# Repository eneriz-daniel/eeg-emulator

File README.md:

# EEG Emulation and Acquisition

> Documentation is available at: [https://eneriz-daniel.com/eeg-emulator/](https://eneriz-daniel.com/eeg-emulator/)

This repository contains the design files, code, and documentation for an EEG
emulation and acquisition system. The system is designed to emulate an EEG headset
using a custom PCB that demultiplexes signals from a National Instruments
USB-6212 Data Acquisition (DAQ) device, and to acquire EEG signals using an ADS1299
Analog-to-Digital Converter (ADC) connected to an Arduino Nano 33 BLE Sense.

## Repository Structure

The repository is organized into the following main directories and files:

- `docs/`: Documentation files for the project
    - `ads1299_driver/`: Python API reference for the ADS1299 driver
    - `assets/`: Images and diagrams used in documentation
    - `datasheets/`: Component datasheets and manuals
  
- `eeg_acquisition/`: EEG signal acquisition system components
    - `ADS1299driver.py`: Python wrapper for the ADS1299 driver
    - `design_files/`: KiCAD PCB and schematic files for the acquisition board
    - `micro/`: Arduino firmware for the ADS1299 driver
        - `src/`: C++ source code for the driver implementation

- `eeg_emulation/`: EEG signal emulation system components
    - `daq.py`: Python script for controlling the NI USB-6212 DAQ
    - `design_files/`: KiCAD PCB and schematic files for the demultiplexer board

- `test.py`: Example script demonstrating the integration between the EEG emulation and acquisition systems, including configuration of the ADS1299, signal generation, data acquisition, and visualization

## Requirements

### Software

- [Python](https://www.python.org/) 3.13 or later (for running the code and documentation)
    - Package manager, [`uv`](https://docs.astral.sh/uv/)
- [KiCAD](https://www.kicad.org/) 9 or later (for PCB design files)
- [PlatformIO](https://platformio.org/) (for Arduino development)

### Commercial hardware

- National Instruments NI USB-6212 Data Acquisition device

## Installation

- Clone the repository:

    ```bash
    git clone https://github.com/eneriz-daniel/eeg-emulator.git
    ```

- Install the required packages:

    ```bash
    uv sync --all-groups
    ```

## Software commands

- To serve the documentation locally:

    ```bash
    uv run mkdocs serve
    ```

- To check linting and formatting:

    ```bash
    uv run ruff check
    ```

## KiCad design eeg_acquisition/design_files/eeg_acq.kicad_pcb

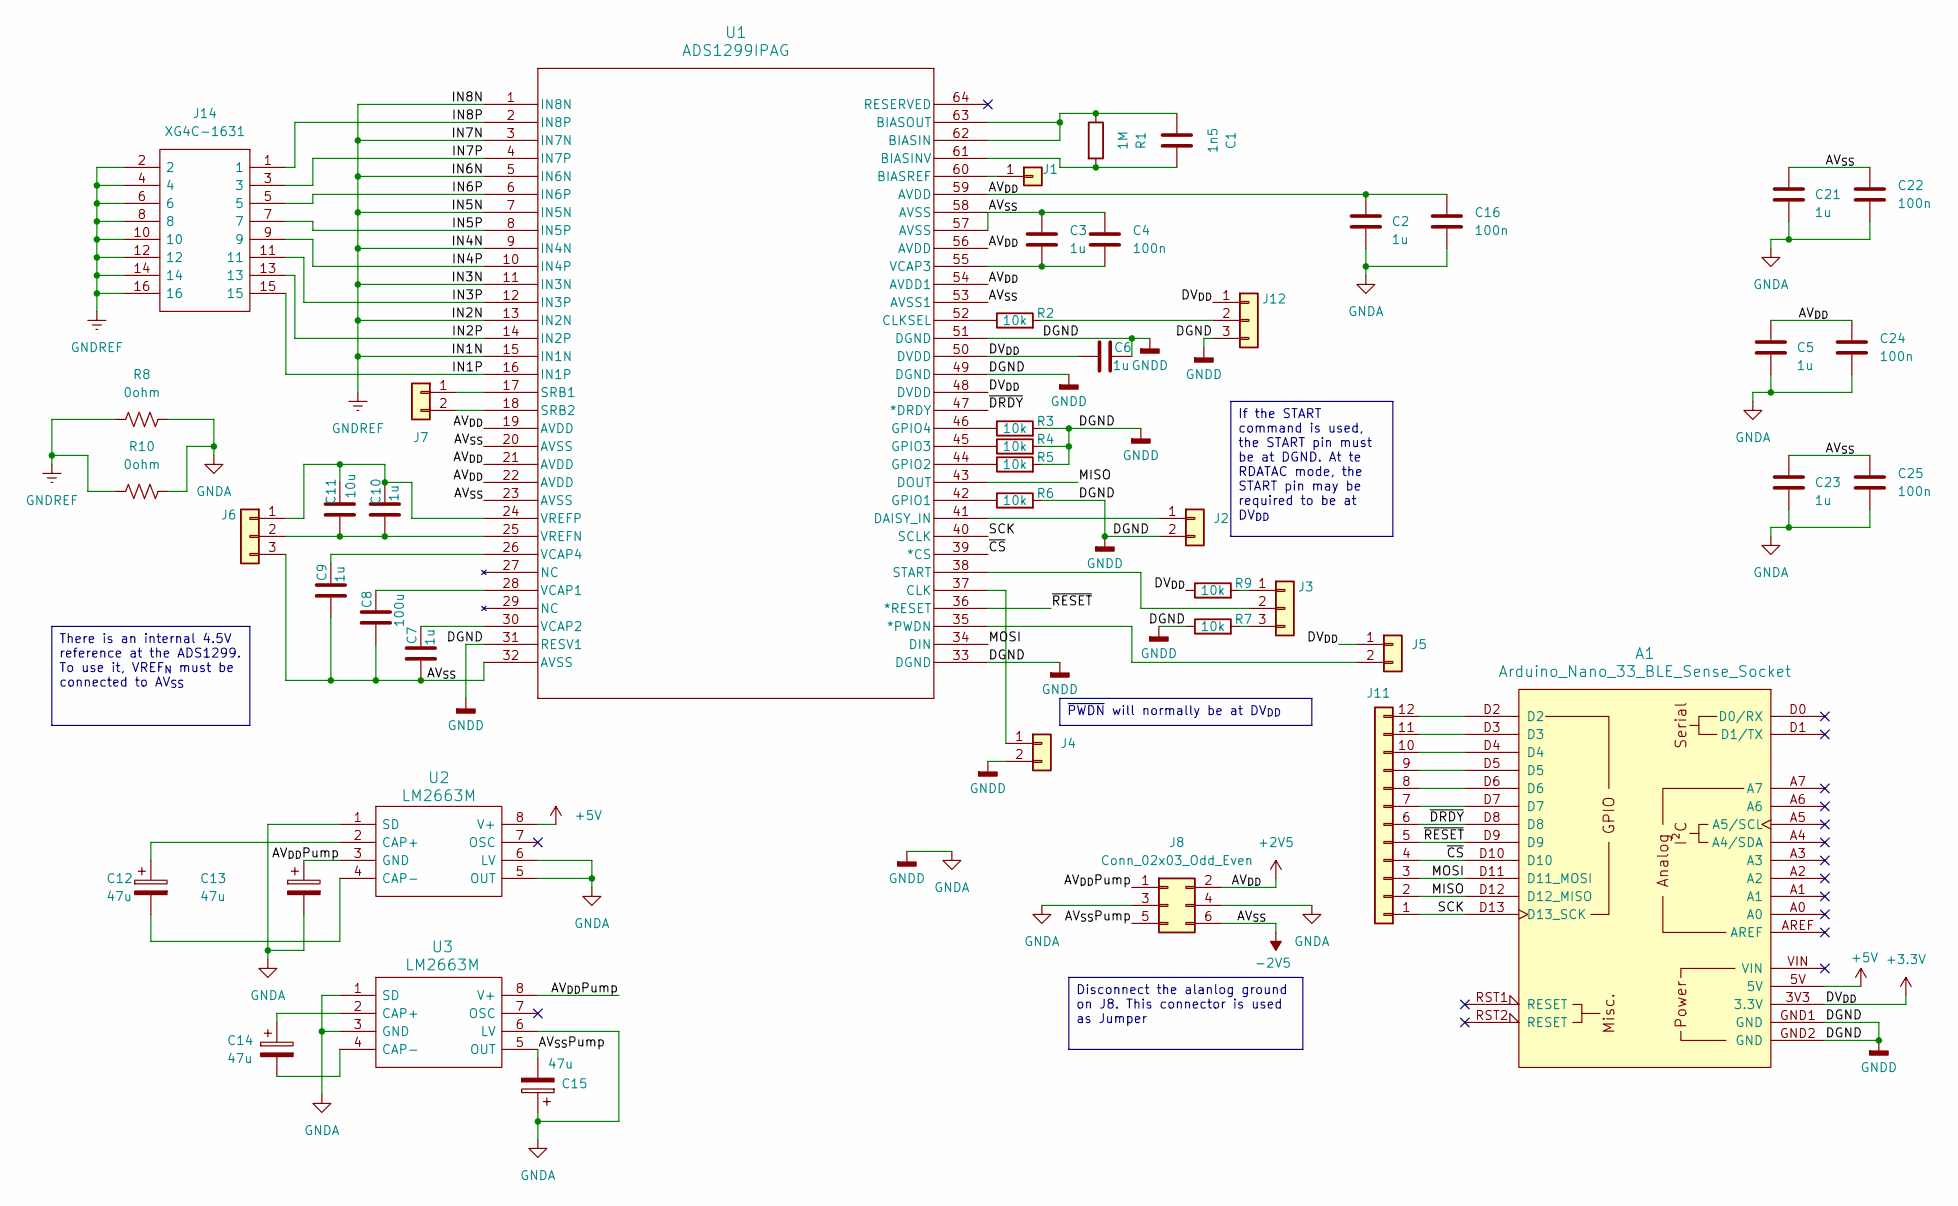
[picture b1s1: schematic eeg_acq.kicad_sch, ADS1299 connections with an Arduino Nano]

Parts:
A1: Arduino_Nano_33_BLE_Sense_Socket; Arduino_Nano_Every_Socket
C1: 1n5; C_0603_1608Metric_Pad1.08x0.95mm_HandSolder
C2, C3, C5, C6, C7, C9, C10, C21, C23: 1u; C_0603_1608Metric_Pad1.08x0.95mm_HandSolder
C4, C16, C22, C24, C25: 100n; C_0603_1608Metric_Pad1.08x0.95mm_HandSolder
C8: 100u; C_1206_3216Metric_Pad1.33x1.80mm_HandSolder
C11: 10u; C_0603_1608Metric_Pad1.08x0.95mm_HandSolder
C12, C13, C14, C15: 47u; CP_Radial_D10.0mm_P5.00mm
J1: BIASREF; PinSocket_1x01_P2.54mm_Vertical
J2, J4: DAISY_IN; PinSocket_1x02_P2.54mm_Vertical
J3: START; PinSocket_1x03_P2.54mm_Vertical
J5: ~PWDN; PinSocket_1x02_P2.54mm_Vertical
J6: VREF; PinSocket_1x03_P2.54mm_Vertical
J7: SRB; PinSocket_1x02_P2.54mm_Vertical
J8: Conn_02x03_Odd_Even; PinHeader_2x03_P2.54mm_Vertical
J11: PinHeader_1x12_P2.54mm_Vertical
J12: CLKSEL; PinSocket_1x03_P2.54mm_Vertical
J14: XG4C-1631; SHDR16W70P254_2X8_2760X850X900P; Manufacturer_Part_Number XG4C-1631; Mouser Part Number 653-XG4C-1631
R1: 1M; R_0603_1608Metric_Pad0.98x0.95mm_HandSolder
R2, R3, R4, R5, R6, R7, R9: 10k; R_0603_1608Metric_Pad0.98x0.95mm_HandSolder
R8, R10: 0ohm; R_0603_1608Metric
U1: ADS1299IPAG; PAG64_TEX
U2, U3: LM2663M; SOIC127P600X175-8N; Manufacturer_Part_Number LM2663M; Mouser Part Number 926-LM2663M

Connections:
+2V5: C2.1, C5.1, C16.1, C24.1, J8.2, U1.19 (AVDD), U1.21 (AVDD), U1.22 (AVDD), U1.54 (AVDD1), U1.56 (AVDD), U1.59 (AVDD)
+3.3V: A1.3V3 (3.3V), C6.2, J5.1, J12.1, R9.1, U1.48 (DVDD), U1.50 (DVDD)
+5V: A1.5V, U2.8 (V+)
-2V5: C3.1, C4.1, C7.2, C8.2, C9.2, C21.1, C22.1, C23.1, C25.1, J6.3, J8.6, U1.20 (AVSS), U1.23 (AVSS), U1.32 (AVSS), U1.53 (AVSS1), U1.57 (AVSS), U1.58 (AVSS)
/AV_{DD}Pump: C13.1, J8.1, U2.3 (GND), U3.8 (V+)
/AV_{SS}Pump: C15.2, J8.5, U3.5 (OUT)
/IN1P: J14.15, U1.16 (IN1P)
/IN2P: J14.13, U1.14 (IN2P)
/IN3P: J14.11, U1.12 (IN3P)
/IN4P: J14.9, U1.10 (IN4P)
/IN5P: J14.7, U1.8 (IN5P)
/IN6P: J14.5, U1.6 (IN6P)
/IN7P: J14.3, U1.4 (IN7P)
/IN8P: J14.1, U1.2 (IN8P)
/MISO: A1.D12 (D12_MISO), J11.2, U1.43 (DOUT)
/MOSI: A1.D11 (D11_MOSI), J11.3, U1.34 (DIN)
/SCK: A1.D13 (D13_SCK), J11.1, U1.40 (SCLK)
/~CS: A1.D10, J11.4, U1.39 (*CS)
/~DRDY: A1.D8, J11.6, U1.47 (*DRDY)
/~RESET: A1.D9, J11.5, U1.36 (*RESET)
GNDA: A1.GND1 (GND), A1.GND2 (GND), C2.2, C5.2, C6.1, C13.2, C15.1, C16.2, C21.2, C22.2, C23.2, C24.2, C25.2, J2.2, J4.2, J8.3, J8.4, J12.3, R3.2, R4.2, R5.2, R6.2, R7.1, R8.2, R10.2, U1.31 (RESV1), U1.33 (DGND), U1.49 (DGND), U1.51 (DGND), U2.1 (SD), U2.5 (OUT), U2.6 (LV), U3.1 (SD), U3.3 (GND), U3.6 (LV)
GNDREF: J14.2, J14.4, J14.6, J14.8, J14.10, J14.12, J14.14, J14.16, R8.1, R10.1, U1.1 (IN8N), U1.3 (IN7N), U1.5 (IN6N), U1.7 (IN5N), U1.9 (IN4N), U1.11 (IN3N), U1.13 (IN2N), U1.15 (IN1N)
unnamed: J1.1, U1.60 (BIASREF)
unnamed: J2.1, U1.41 (DAISY_IN)
unnamed: J3.1, R9.2
unnamed: J3.2, U1.38 (START)
unnamed: J3.3, R7.2
unnamed: J4.1, U1.37 (CLK)
unnamed: J5.2, U1.35 (*PWDN)
unnamed: C10.1, C11.1, J6.1, U1.24 (VREFP)
unnamed: C10.2, C11.2, J6.2, U1.25 (VREFN)
unnamed: J7.1, U1.17 (SRB1)
unnamed: J7.2, U1.18 (SRB2)
unnamed: A1.D7, J11.7
unnamed: A1.D6, J11.8
unnamed: A1.D5, J11.9
unnamed: A1.D4, J11.10
unnamed: A1.D3, J11.11
unnamed: A1.D2, J11.12
unnamed: J12.2, R2.2
unnamed: C1.1, R1.1, U1.62 (BIASIN), U1.63 (BIASOUT)
unnamed: C1.2, R1.2, U1.61 (BIASINV)
unnamed: R2.1, U1.52 (CLKSEL)
unnamed: R6.1, U1.42 (GPIO1)
unnamed: R5.1, U1.44 (GPIO2)
unnamed: R4.1, U1.45 (GPIO3)
unnamed: R3.1, U1.46 (GPIO4)
unnamed: C8.1, U1.28 (VCAP1)
unnamed: C7.1, U1.30 (VCAP2)
unnamed: C3.2, C4.2, U1.55 (VCAP3)
unnamed: C9.1, U1.26 (VCAP4)
unnamed: C12.1, U2.2 (CAP+)
unnamed: C12.2, U2.4 (CAP-)
unnamed: C14.1, U3.2 (CAP+)
unnamed: C14.2, U3.4 (CAP-)

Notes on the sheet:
~{PWDN} will normally be at DV_{DD}
Disconnect the alanlog ground on J8. This connector is used as Jumper
If the START command is used, the START pin must be at DGND. At te RDATAC mode, the START pin may be required to be at DV_{DD}
There is an internal 4.5V reference at the ADS1299. To use it, VREF_{N} must be connected to AV_{SS}

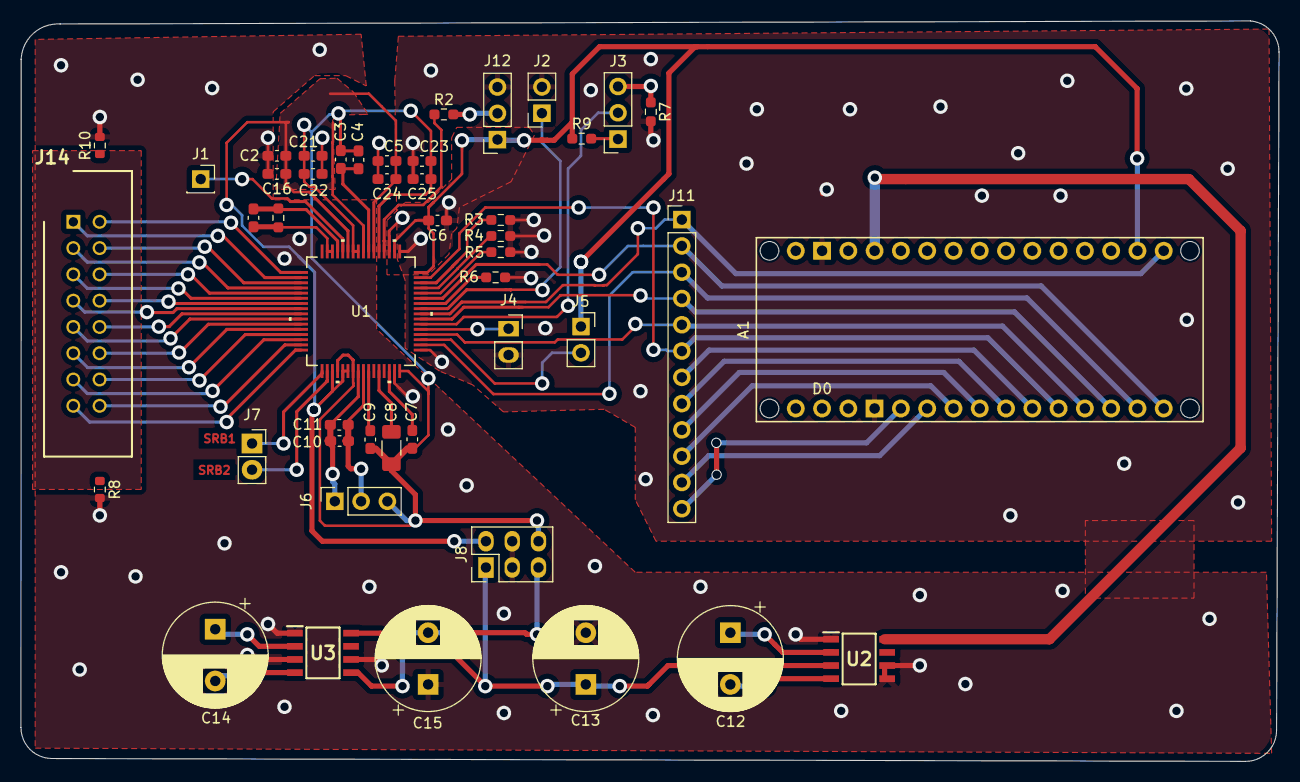
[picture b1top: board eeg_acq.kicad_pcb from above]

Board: 2 copper layers, 121.6 x 71.6 mm, 46 parts (0 on the bottom side), 55 nets.

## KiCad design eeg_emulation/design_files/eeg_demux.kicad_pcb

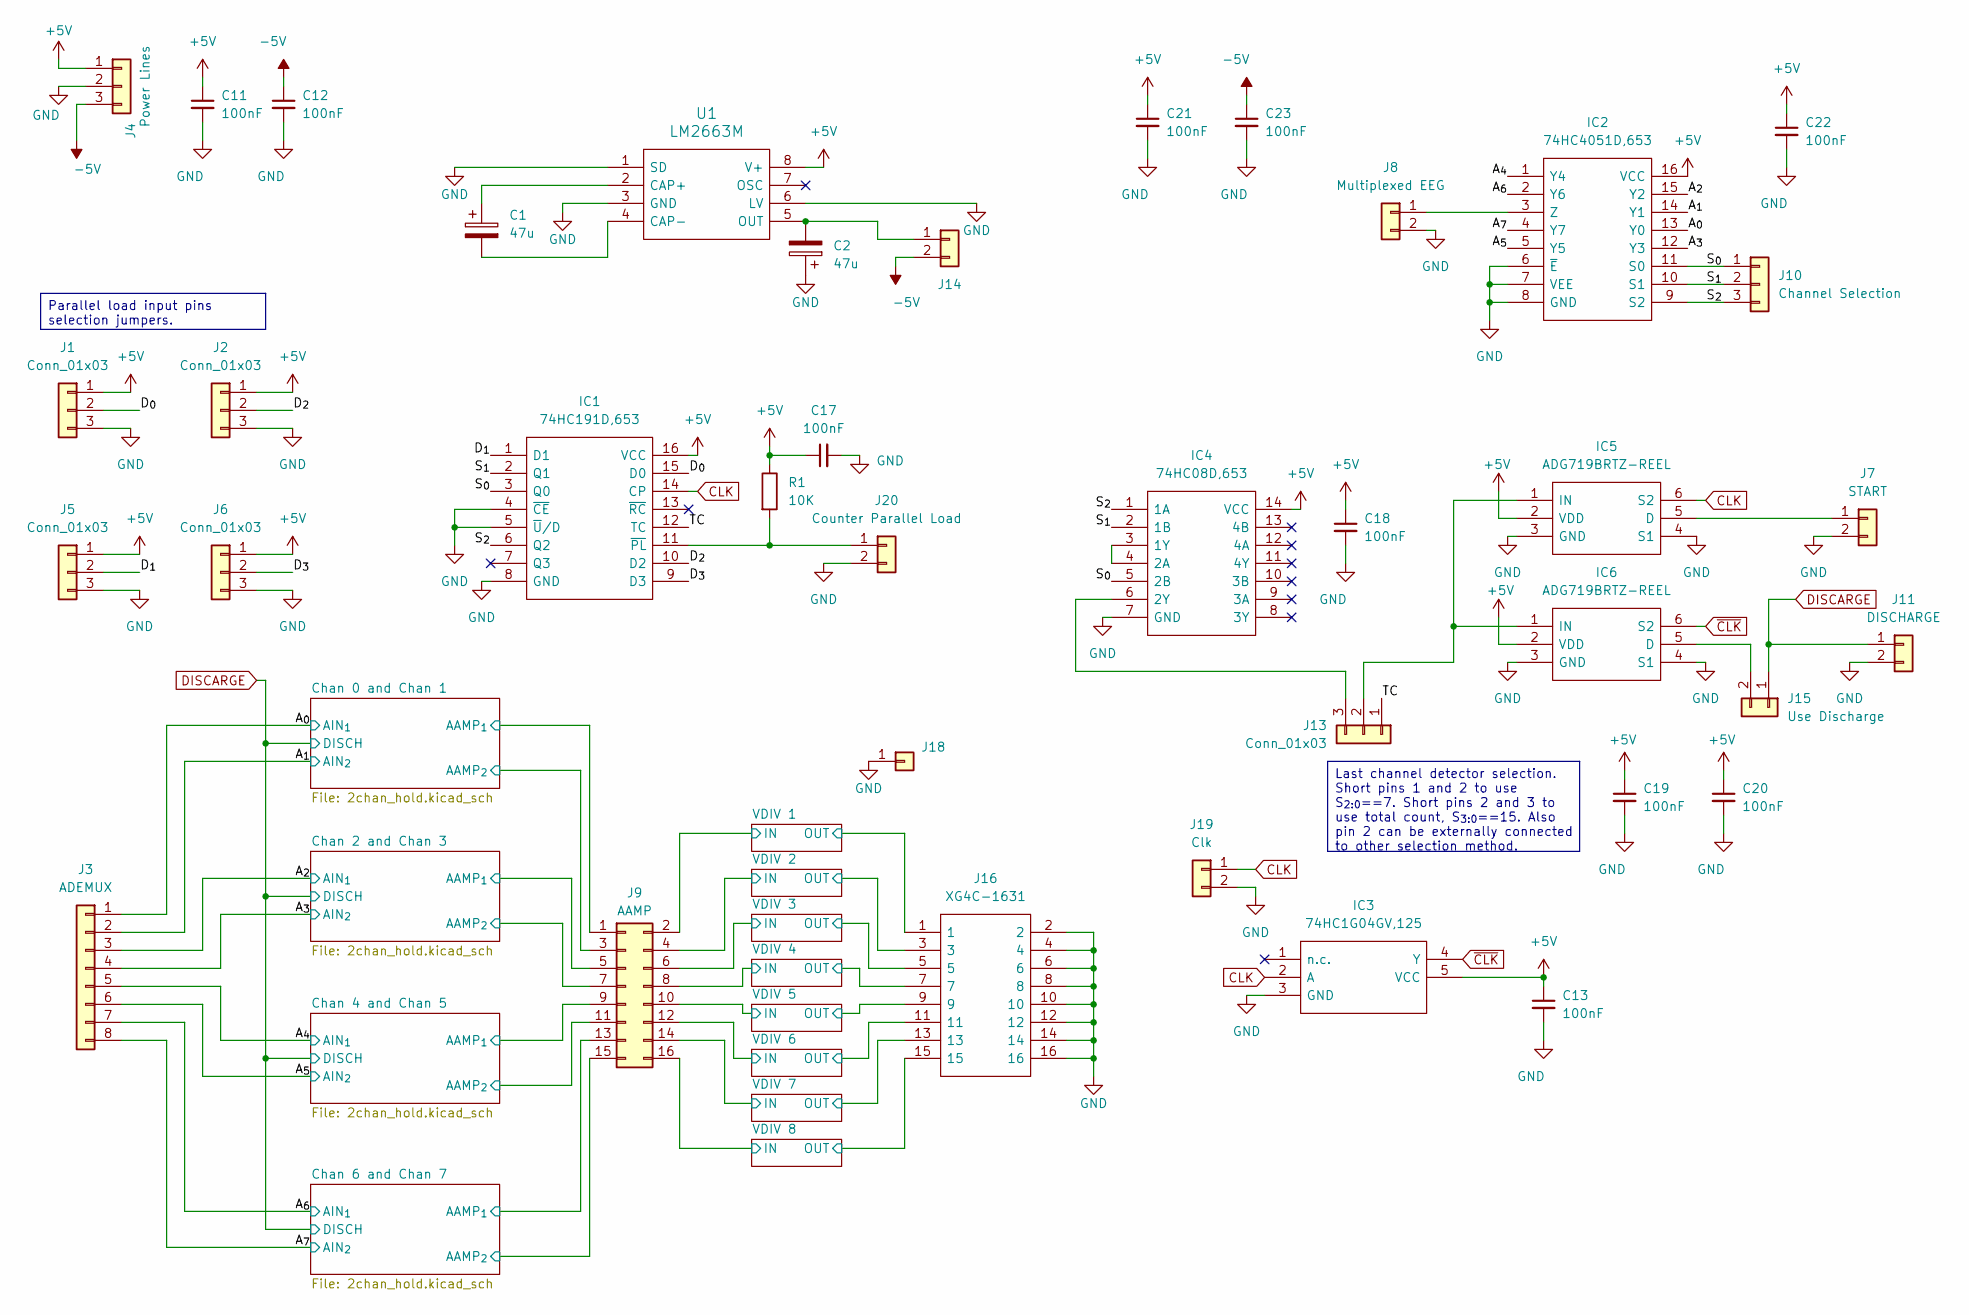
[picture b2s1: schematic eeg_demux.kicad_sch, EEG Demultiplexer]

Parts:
C1, C2: 47u; CP_Radial_D10.0mm_P5.00mm
C11, C12, C13, C17, C18, C19, C20, C21, C22, C23: 100nF; C_1206_3216Metric_Pad1.33x1.80mm_HandSolder
IC1: 74HC191D,653; SOIC127P600X175-16N; Mouser Part Number 771-HC191D653
IC2: 74HC4051D,653; 74HC4051D653; Mouser Part Number 771-74HC4051D-T
IC3: 74HC1G04GV,125; SOT95P275X110-5N; Mouser Part Number 771-74HC1G04GV
IC4: 74HC08D,653; SOIC127P600X175-14N; Mouser Part Number 771-74HC08D-T
IC5, IC6: ADG719BRTZ-REEL; SOT95P280X145-6N; Mouser Part Number 584-ADG719BRTZ-R
J1, J2, J5, J6, J13: Conn_01x03; PinHeader_1x03_P2.54mm_Vertical
J3: ADEMUX; PinHeader_1x08_P2.54mm_Vertical
J4: Power Lines; PinHeader_1x03_P2.54mm_Vertical
J7: START; PinHeader_1x02_P2.54mm_Vertical
J8: Multiplexed EEG; PinHeader_1x02_P2.54mm_Vertical
J9: AAMP; PinHeader_2x08_P2.54mm_Vertical
J10: Channel Selection; PinHeader_1x03_P2.54mm_Vertical
J11: DISCHARGE; PinHeader_1x02_P2.54mm_Vertical
J14: PinHeader_1x02_P2.54mm_Vertical
J15: Use Discharge; PinHeader_1x02_P2.54mm_Vertical
J16: XG4C-1631; SHDR16W70P254_2X8_2760X850X900P; Manufacturer_Part_Number XG4C-1631; Mouser Part Number 653-XG4C-1631
J18: PinHeader_1x01_P2.54mm_Vertical
J19: Clk; PinHeader_1x02_P2.54mm_Vertical
J20: Counter Parallel Load; PinHeader_1x02_P2.54mm_Vertical
R1: 10K; R_0603_1608Metric_Pad0.98x0.95mm_HandSolder
U1: LM2663M; SOIC127P600X175-8N; Manufacturer_Part_Number LM2663M; Mouser Part Number 926-LM2663M

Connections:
+5V: C11.1, C13.1, C17.1, C18.1, C19.1, C20.1, C21.1, C22.1, IC1.16 (VCC), IC2.16 (VCC), IC3.5 (VCC), IC4.14 (VCC), IC5.2 (VDD), IC6.2 (VDD), J1.1, J2.1, J4.1, J5.1, J6.1, R1.1, U1.8 (V+); also elsewhere on the board
-5V: C12.1, C23.1, J4.3, J14.2; also elsewhere on the board
/A_{0}: IC2.13 (Y0), J3.1; also elsewhere on the board
/A_{1}: IC2.14 (Y1), J3.2; also elsewhere on the board
/A_{2}: IC2.15 (Y2), J3.3; also elsewhere on the board
/A_{3}: IC2.12 (Y3), J3.4; also elsewhere on the board
/A_{4}: IC2.1 (Y4), J3.5; also elsewhere on the board
/A_{5}: IC2.5 (Y5), J3.6; also elsewhere on the board
/A_{6}: IC2.2 (Y6), J3.7; also elsewhere on the board
/A_{7}: IC2.4 (Y7), J3.8; also elsewhere on the board
/Chan 0 and Chan 1/AAMP_{1}: J9.1; also elsewhere on the board
/Chan 0 and Chan 1/AAMP_{2}: J9.3; also elsewhere on the board
/Chan 2 and Chan 3/AAMP_{1}: J9.5; also elsewhere on the board
/Chan 2 and Chan 3/AAMP_{2}: J9.7; also elsewhere on the board
/Chan 4 and Chan 5/AAMP_{1}: J9.9; also elsewhere on the board
/Chan 4 and Chan 5/AAMP_{2}: J9.11; also elsewhere on the board
/Chan 6 and Chan 7/AAMP_{1}: J9.13; also elsewhere on the board
/Chan 6 and Chan 7/AAMP_{2}: J9.15; also elsewhere on the board
/D_{0}: IC1.15 (D0), J1.2
/D_{1}: IC1.1 (D1), J5.2
/D_{2}: IC1.10 (D2), J2.2
/D_{3}: IC1.9 (D3), J6.2
/S_{0}: IC1.3 (Q0), IC2.11 (S0), IC4.5 (2B), J10.1
/S_{1}: IC1.2 (Q1), IC2.10 (S1), IC4.2 (1B), J10.2
/S_{2}: IC1.6 (Q2), IC2.9 (S2), IC4.1 (1A), J10.3
/TC: IC1.12 (TC), J13.1
/VDIV 1/IN: J9.2; also elsewhere on the board
/VDIV 1/OUT: J16.1; also elsewhere on the board
/VDIV 2/IN: J9.4; also elsewhere on the board
/VDIV 2/OUT: J16.3; also elsewhere on the board
/VDIV 3/IN: J9.6; also elsewhere on the board
/VDIV 3/OUT: J16.5; also elsewhere on the board
/VDIV 4/IN: J9.8; also elsewhere on the board
/VDIV 4/OUT: J16.7; also elsewhere on the board
/VDIV 5/IN: J9.10; also elsewhere on the board
/VDIV 5/OUT: J16.9; also elsewhere on the board
/VDIV 6/IN: J9.12; also elsewhere on the board
/VDIV 6/OUT: J16.11; also elsewhere on the board
/VDIV 7/IN: J9.14; also elsewhere on the board
/VDIV 7/OUT: J16.13; also elsewhere on the board
/VDIV 8/IN: J9.16; also elsewhere on the board
/VDIV 8/OUT: J16.15; also elsewhere on the board
CLK: IC1.14 (CP), IC3.2 (A), IC5.6 (S2), J19.1
DISCARGE: J11.1, J15.1; also elsewhere on the board
GND: C2.1, C11.2, C12.2, C13.2, C17.2, C18.2, C19.2, C20.2, C21.2, C22.2, C23.2, IC1.4 (~CE), IC1.5 (~U/D), IC1.8 (GND), IC2.6 (~E), IC2.7 (VEE), IC2.8 (GND), IC3.3 (GND), IC4.7 (GND), IC5.3 (GND), IC5.4 (S1), IC6.3 (GND), IC6.4 (S1), J1.3, J2.3, J4.2, J5.3, J6.3, J7.2, J8.2, J11.2, J16.2, J16.4, J16.6, J16.8, J16.10, J16.12, J16.14, J16.16, J18.1, J19.2, J20.2, U1.1 (SD), U1.3 (GND), U1.6 (LV); also elsewhere on the board
unnamed: IC1.11 (~PL), J20.1, R1.2
unnamed: IC2.3 (Z), J8.1
unnamed: IC4.3 (1Y), IC4.4 (2A)
unnamed: IC4.6 (2Y), J13.3
unnamed: IC5.5 (D), J7.1
unnamed: IC5.1 (IN), IC6.1 (IN), J13.2
unnamed: IC6.5 (D), J15.2
unnamed: C2.2, J14.1, U1.5 (OUT)
unnamed: C1.1, U1.2 (CAP+)
unnamed: C1.2, U1.4 (CAP-)
~CLK: IC3.4 (Y), IC6.6 (S2)

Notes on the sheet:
Last channel detector selection. Short pins 1 and 2 to use S_{2:0}==7. Short pins 2 and 3 to use total count, S_{3:0}==15. Also pin 2 can be externally connected to other selection method.
Parallel load input pins selection jumpers.

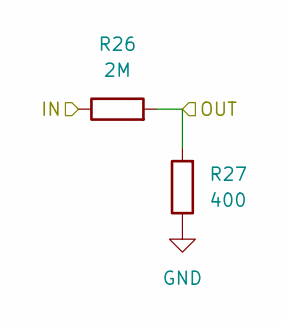
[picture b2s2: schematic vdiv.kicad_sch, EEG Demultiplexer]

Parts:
R26: 2M; R_0603_1608Metric_Pad0.98x0.95mm_HandSolder
R27: 400; R_0603_1608Metric_Pad0.98x0.95mm_HandSolder

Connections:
/VDIV 1/IN: R26.1; also elsewhere on the board
/VDIV 1/OUT: R26.2, R27.2; also elsewhere on the board
GND: R27.1; also elsewhere on the board

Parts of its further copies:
R28, R30, R32, R34, R36, R38, R40: 2M; R_0603_1608Metric_Pad0.98x0.95mm_HandSolder
R29, R31, R33, R35, R37, R39, R41: 400; R_0603_1608Metric_Pad0.98x0.95mm_HandSolder

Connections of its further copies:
/VDIV 2/IN: R28.1; also elsewhere on the board
/VDIV 2/OUT: R28.2, R29.2; also elsewhere on the board
/VDIV 3/IN: R30.1; also elsewhere on the board
/VDIV 3/OUT: R30.2, R31.2; also elsewhere on the board
/VDIV 4/IN: R32.1; also elsewhere on the board
/VDIV 4/OUT: R32.2, R33.2; also elsewhere on the board
/VDIV 5/IN: R34.1; also elsewhere on the board
/VDIV 5/OUT: R34.2, R35.2; also elsewhere on the board
/VDIV 6/IN: R36.1; also elsewhere on the board
/VDIV 6/OUT: R36.2, R37.2; also elsewhere on the board
/VDIV 7/IN: R38.1; also elsewhere on the board
/VDIV 7/OUT: R38.2, R39.2; also elsewhere on the board
/VDIV 8/IN: R40.1; also elsewhere on the board
/VDIV 8/OUT: R40.2, R41.2; also elsewhere on the board
GND: R29.1, R31.1, R33.1, R35.1, R37.1, R39.1, R41.1; also elsewhere on the board

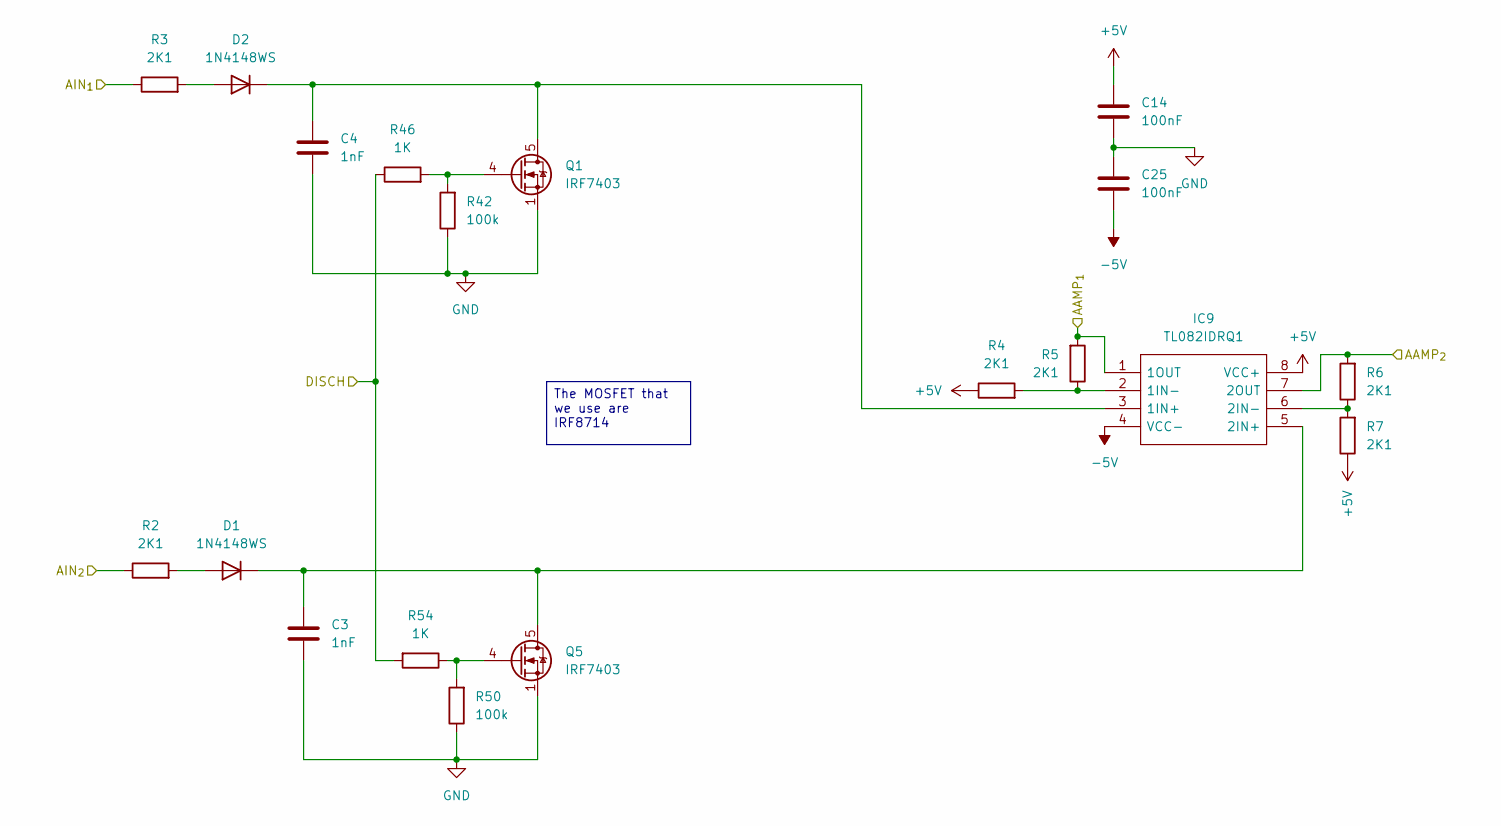
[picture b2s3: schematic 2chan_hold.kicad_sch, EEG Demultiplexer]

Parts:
C3, C4: 1nF; C_0603_1608Metric_Pad1.08x0.95mm_HandSolder
C14, C25: 100nF; C_0603_1608Metric_Pad1.08x0.95mm_HandSolder
D1, D2: 1N4148WS; D_1206_3216Metric_Pad1.42x1.75mm_HandSolder
IC9: TL082IDRQ1; SOIC127P600X175-8N; Mouser Part Number 595-TL082IDRQ1
Q1, Q5: IRF7403; SOIC-8_3.9x4.9mm_P1.27mm
R2, R3, R4, R5, R6, R7: 2K1; R_0603_1608Metric_Pad0.98x0.95mm_HandSolder
R42, R50: 100k; R_0603_1608Metric_Pad0.98x0.95mm_HandSolder
R46, R54: 1K; R_0603_1608Metric_Pad0.98x0.95mm_HandSolder

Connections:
+5V: C14.1, IC9.8 (VCC+), R4.1, R7.1; also elsewhere on the board
-5V: C25.2, IC9.4 (VCC-); also elsewhere on the board
/A_{0}: R3.1; also elsewhere on the board
/A_{1}: R2.1; also elsewhere on the board
/Chan 0 and Chan 1/AAMP_{1}: IC9.1 (1OUT), R5.2; also elsewhere on the board
/Chan 0 and Chan 1/AAMP_{2}: IC9.7 (2OUT), R6.2; also elsewhere on the board
DISCARGE: R46.1, R54.2; also elsewhere on the board
GND: C3.2, C4.2, C14.2, C25.1, Q1.1 (S), Q1.2 (S), Q1.3 (S), Q5.1 (S), Q5.2 (S), Q5.3 (S), R42.1, R50.1; also elsewhere on the board
unnamed: D1.2 (A), R2.2
unnamed: C3.1, D1.1 (K), IC9.5 (2IN+), Q5.5 (D), Q5.6 (D), Q5.7 (D), Q5.8 (D)
unnamed: D2.2 (A), R3.2
unnamed: C4.1, D2.1 (K), IC9.3 (1IN+), Q1.5 (D), Q1.6 (D), Q1.7 (D), Q1.8 (D)
unnamed: IC9.2 (1IN-), R4.2, R5.1
unnamed: IC9.6 (2IN-), R6.1, R7.2
unnamed: Q1.4 (G), R42.2, R46.2
unnamed: Q5.4 (G), R50.2, R54.1

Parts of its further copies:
C5, C6, C7, C8, C9, C10: 1nF; C_0603_1608Metric_Pad1.08x0.95mm_HandSolder
C15, C16, C24, C26, C27, C28: 100nF; C_0603_1608Metric_Pad1.08x0.95mm_HandSolder
D3, D4, D5, D6, D7, D8: 1N4148WS; D_1206_3216Metric_Pad1.42x1.75mm_HandSolder
IC12, IC15, IC18: TL082IDRQ1; SOIC127P600X175-8N; Mouser Part Number 595-TL082IDRQ1
Q2, Q3, Q4, Q6, Q7, Q8: IRF7403; SOIC-8_3.9x4.9mm_P1.27mm
R8, R9, R10, R11, R12, R13, R14, R15, R16, R17, R18, R19, R20, R21, R22, R23, R24, R25: 2K1; R_0603_1608Metric_Pad0.98x0.95mm_HandSolder
R43, R44, R45, R51, R52, R53: 100k; R_0603_1608Metric_Pad0.98x0.95mm_HandSolder
R47, R48, R49, R55, R56, R57: 1K; R_0603_1608Metric_Pad0.98x0.95mm_HandSolder

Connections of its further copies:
+5V: C15.1, C16.1, C24.1, IC12.8 (VCC+), IC15.8 (VCC+), IC18.8 (VCC+), R10.1, R13.1, R16.1, R19.1, R22.1, R25.1; also elsewhere on the board
-5V: C26.2, C27.2, C28.2, IC12.4 (VCC-), IC15.4 (VCC-), IC18.4 (VCC-); also elsewhere on the board
/A_{2}: R9.1; also elsewhere on the board
/A_{3}: R8.1; also elsewhere on the board
/A_{4}: R15.1; also elsewhere on the board
/A_{5}: R14.1; also elsewhere on the board
/A_{6}: R21.1; also elsewhere on the board
/A_{7}: R20.1; also elsewhere on the board
/Chan 2 and Chan 3/AAMP_{1}: IC12.1 (1OUT), R11.2; also elsewhere on the board
/Chan 2 and Chan 3/AAMP_{2}: IC12.7 (2OUT), R12.2; also elsewhere on the board
/Chan 4 and Chan 5/AAMP_{1}: IC15.1 (1OUT), R17.2; also elsewhere on the board
/Chan 4 and Chan 5/AAMP_{2}: IC15.7 (2OUT), R18.2; also elsewhere on the board
/Chan 6 and Chan 7/AAMP_{1}: IC18.1 (1OUT), R23.2; also elsewhere on the board
/Chan 6 and Chan 7/AAMP_{2}: IC18.7 (2OUT), R24.2; also elsewhere on the board
DISCARGE: R47.1, R48.1, R49.1, R55.2, R56.2, R57.2; also elsewhere on the board
GND: C5.2, C6.2, C7.2, C8.2, C9.2, C10.2, C15.2, C16.2, C24.2, C26.1, C27.1, C28.1, Q2.1 (S), Q2.2 (S), Q2.3 (S), Q3.1 (S), Q3.2 (S), Q3.3 (S), Q4.1 (S), Q4.2 (S), Q4.3 (S), Q6.1 (S), Q6.2 (S), Q6.3 (S), Q7.1 (S), Q7.2 (S), Q7.3 (S), Q8.1 (S), Q8.2 (S), Q8.3 (S), R43.1, R44.1, R45.1, R51.1, R52.1, R53.1; also elsewhere on the board
unnamed: D3.2 (A), R8.2
unnamed: C5.1, D3.1 (K), IC12.5 (2IN+), Q6.5 (D), Q6.6 (D), Q6.7 (D), Q6.8 (D)
unnamed: D4.2 (A), R9.2
unnamed: C6.1, D4.1 (K), IC12.3 (1IN+), Q2.5 (D), Q2.6 (D), Q2.7 (D), Q2.8 (D)
unnamed: D5.2 (A), R14.2
unnamed: C7.1, D5.1 (K), IC15.5 (2IN+), Q7.5 (D), Q7.6 (D), Q7.7 (D), Q7.8 (D)
unnamed: D6.2 (A), R15.2
unnamed: C8.1, D6.1 (K), IC15.3 (1IN+), Q3.5 (D), Q3.6 (D), Q3.7 (D), Q3.8 (D)
unnamed: D7.2 (A), R20.2
unnamed: C9.1, D7.1 (K), IC18.5 (2IN+), Q8.5 (D), Q8.6 (D), Q8.7 (D), Q8.8 (D)
unnamed: D8.2 (A), R21.2
unnamed: C10.1, D8.1 (K), IC18.3 (1IN+), Q4.5 (D), Q4.6 (D), Q4.7 (D), Q4.8 (D)
unnamed: IC12.2 (1IN-), R10.2, R11.1
unnamed: IC12.6 (2IN-), R12.1, R13.2
unnamed: IC15.2 (1IN-), R16.2, R17.1
unnamed: IC15.6 (2IN-), R18.1, R19.2
unnamed: IC18.2 (1IN-), R22.2, R23.1
unnamed: IC18.6 (2IN-), R24.1, R25.2
unnamed: Q2.4 (G), R43.2, R47.2
unnamed: Q3.4 (G), R44.2, R48.2
unnamed: Q4.4 (G), R45.2, R49.2
unnamed: Q6.4 (G), R51.2, R55.1
unnamed: Q7.4 (G), R52.2, R56.1
unnamed: Q8.4 (G), R53.2, R57.1

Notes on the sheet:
The MOSFET that we use are IRF8714

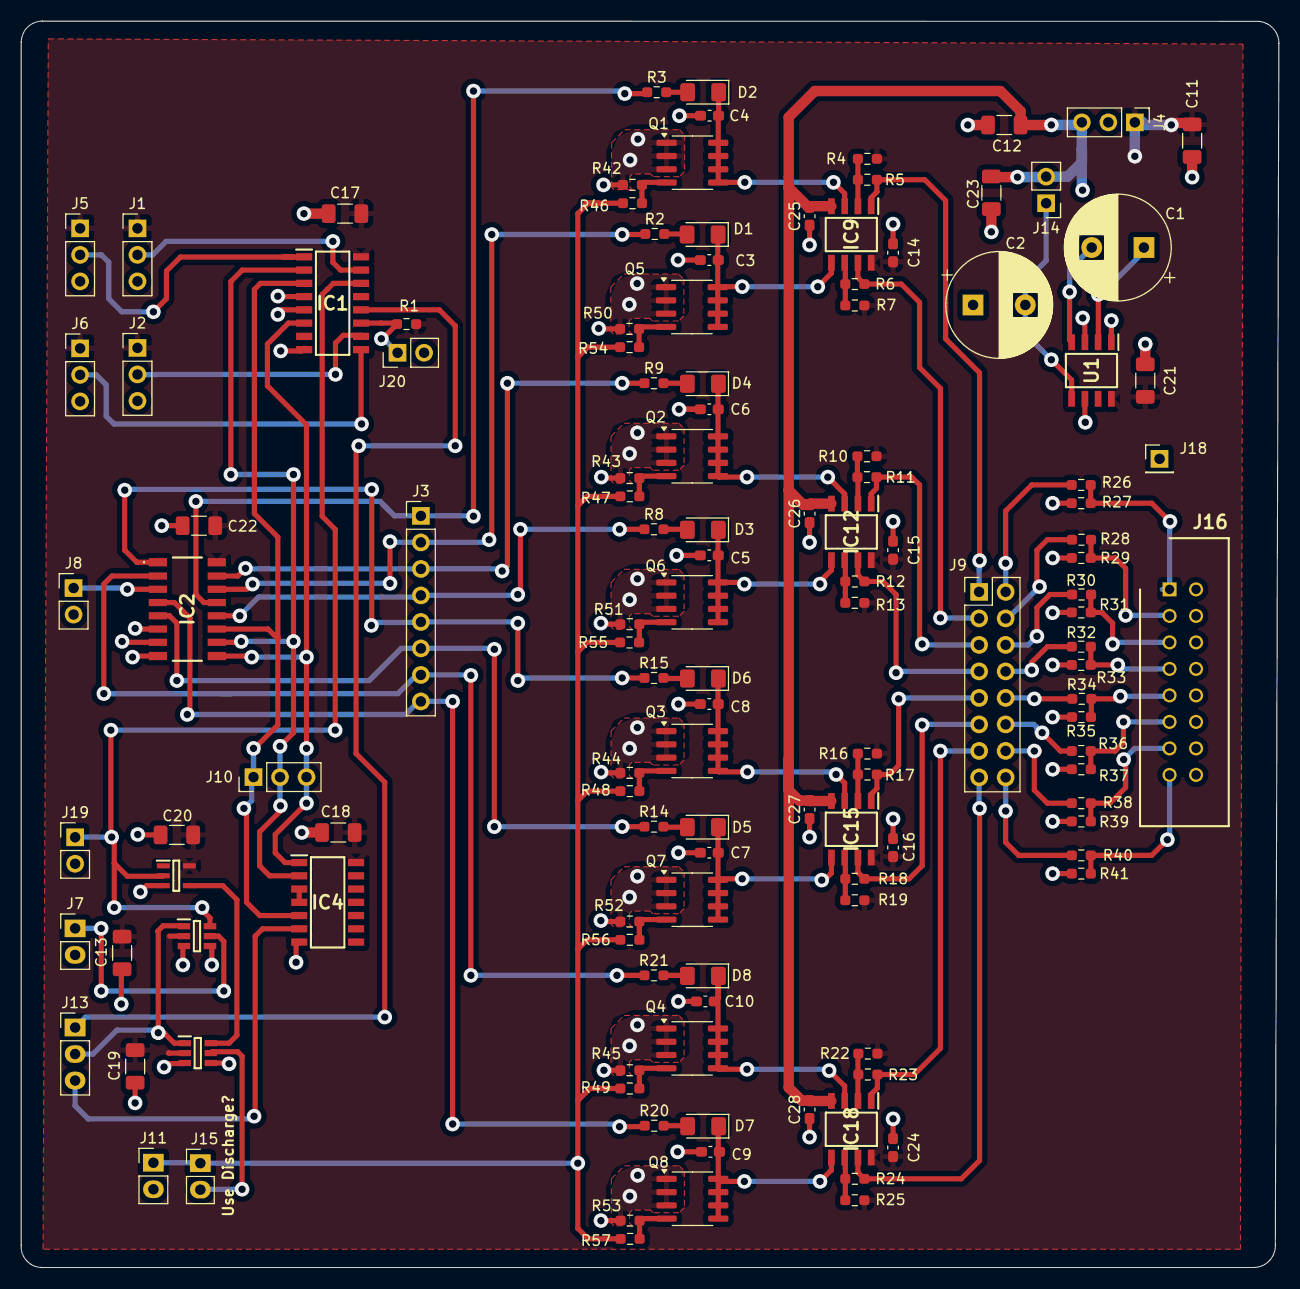
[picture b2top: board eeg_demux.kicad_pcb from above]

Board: 2 copper layers, 120.5 x 119.4 mm, 130 parts (0 on the bottom side), 88 nets.

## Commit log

2025-10-30 Deployed with MkDocs version: 1.6.1
2025-10-30 feat: first commit
2025-10-30 Deployed b72c9a7 with MkDocs version: 1.6.1
2025-10-30 chore: remove site from master
2025-10-30 fix: update repository clone URL and add documentation link
2026-04-15 feat: add Figure 9
